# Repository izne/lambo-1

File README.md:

# lambo-1
Vacuum tube audio (low frequency power) amplifier
Class A single ended
No negative feedback
ECL 86 Pentode in Triode mode 
Open Hardware

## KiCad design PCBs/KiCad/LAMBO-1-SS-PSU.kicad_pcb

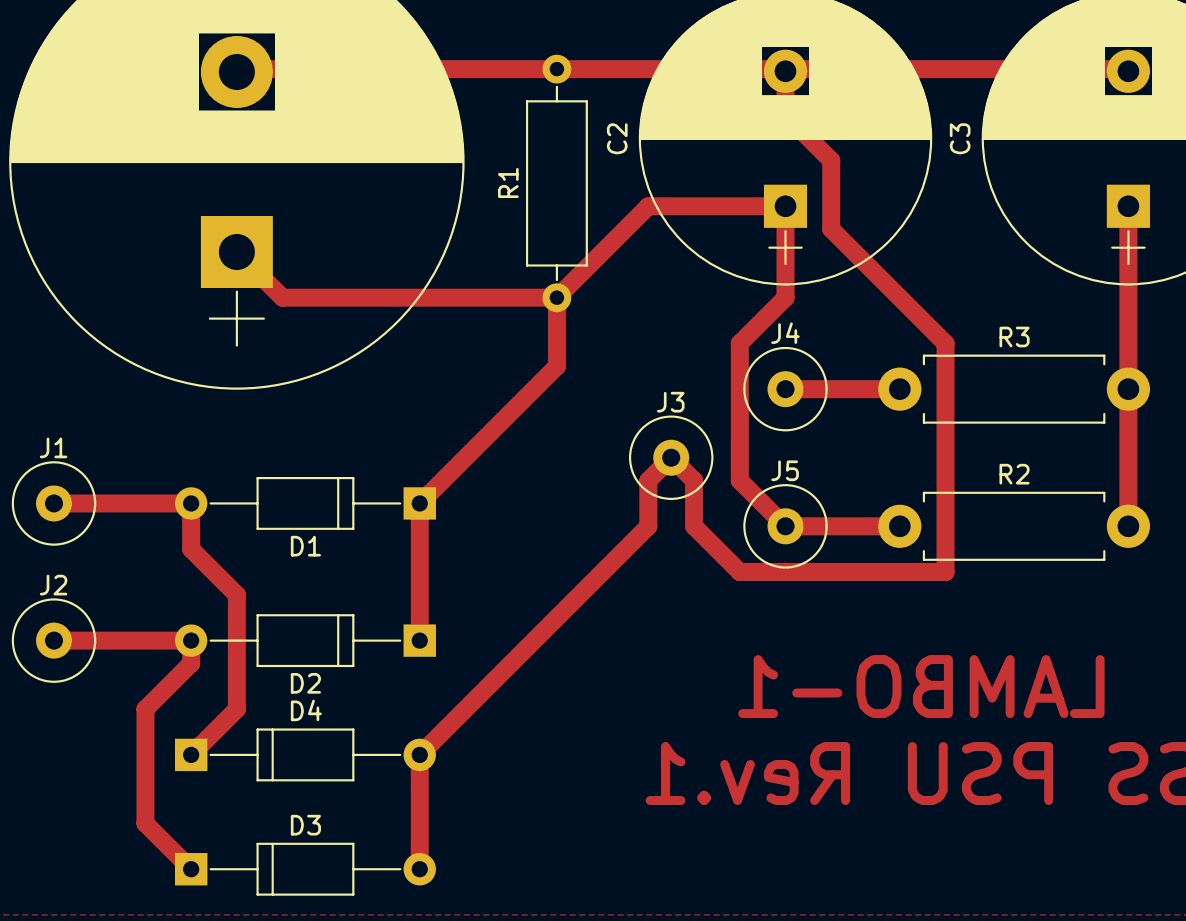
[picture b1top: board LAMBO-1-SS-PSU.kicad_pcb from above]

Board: 2 copper layers, 15 parts (0 on the bottom side), 6 nets.

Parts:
C1: CP; CP_Radial_D25.0mm_P10.00mm_SnapIn
C2, C3: CP; CP_Radial_D16.0mm_P7.50mm
D1, D2, D3, D4: D_ALT; D_A-405_P12.70mm_Horizontal
J1, J2: 245 VAC; 1pin
J3: GND; 1pin
J4: 170 VDC; 1pin
J5: 320 VDC; 1pin
R1: R; R_Axial_DIN0309_L9.0mm_D3.2mm_P12.70mm_Horizontal
R2, R3: R; R_Axial_DIN0411_L9.9mm_D3.6mm_P12.70mm_Horizontal

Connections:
unnamed: C1.1, C2.1, D1.1, D2.1, J5.1, R1.1, R2.1
unnamed: C1.2, C2.2, C3.2, D3.2, D4.2, J3.1, R1.2
unnamed: C3.1, R2.2, R3.2
unnamed: D1.2, D4.1, J1.1
unnamed: D2.2, D3.1, J2.1
unnamed: J4.1, R3.1

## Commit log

2015-11-11 Init
2015-11-11 Capacitor values added
2015-11-18 fixes and labeling. psu rev 3. audio rev 4
2015-11-18 resistor values R4, R5 and R6
2015-11-29 Updated resistor values. Corrected power supply voltage after loading with the end stage.
2015-11-30 PNG update
2015-12-06 Preamp sensitivity mod.
2015-12-06 Fixed wiring
2015-12-06 Fixed C1 and C2 voltages
2016-03-03 Added component values based on prototype tests
2016-03-04 Added supplemental files
    FreeCAD chassis design
    XLS file with calculations
    Scan of a draft with calculations
    ECL86 pentode as triode performance lines
2016-03-12 Added LTspice files
2016-03-13 Added sim screenshot
2017-04-17 Changed power transformer. Modified signal for higher voltage, cleanup. Modified PSU to include triode voltage filtering.
2017-05-01 Added cathode capacitor in pre-tube
2017-11-04 added some references
2017-11-04 added first revision PCB board (schematic, netlist, dsn, etc.) for the solid statue power supply made in KiCad
2017-12-11 Set theme jekyll-theme-cayman
2019-10-13 Just some clarifications
